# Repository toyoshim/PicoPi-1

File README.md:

# PicoPi-1
PDP-1 emulator, running on Raspberry Pi Pico, written in Rust.
See my [tweet](https://twitter.com/toyoshim/status/1591306173504188417?s=20&t=RCzo7QGhFZNQS9Ckd0akRA) to know how it looks like.

## Repository
This repository contains a KiCAD project, schematics and gerber data, for  the
DAC to covert X/Y CRT position in 10-bits ditial to analog signals so that
oscilloscopes can show picture in the XY mode.

Also, you can find a firmware under the `firmware` directory. It is written in
Rust, and you may need some setup to build it. This document doesn't explain
details (because I remember only partial setups...).

The project expects VS Code with some Extensions to develop ARM based processors
with openocd.

## TODO
- Speed control: now the emulation core counts cycles, but doesn't synchronized
with real timer. So, it runs a little faster than the original PDP-1.
- Game controller: yes, I know what I should do, but didn't implement it yet.
See my TODO comment in pdp1.rs's IOT instruction handling.
- Snowflake support: PDP-1 emulation core may have a bug around ALU as the
snowflake shows broken images. I have a working C++ version. So, it can be fixed
soon.
- Rust readability: as I'm new to Rust, the code still doesn't look so nice.
- Documents: agreed...

*CATS: ALL YOUR `PR` ARE WELCOMED TO US.*

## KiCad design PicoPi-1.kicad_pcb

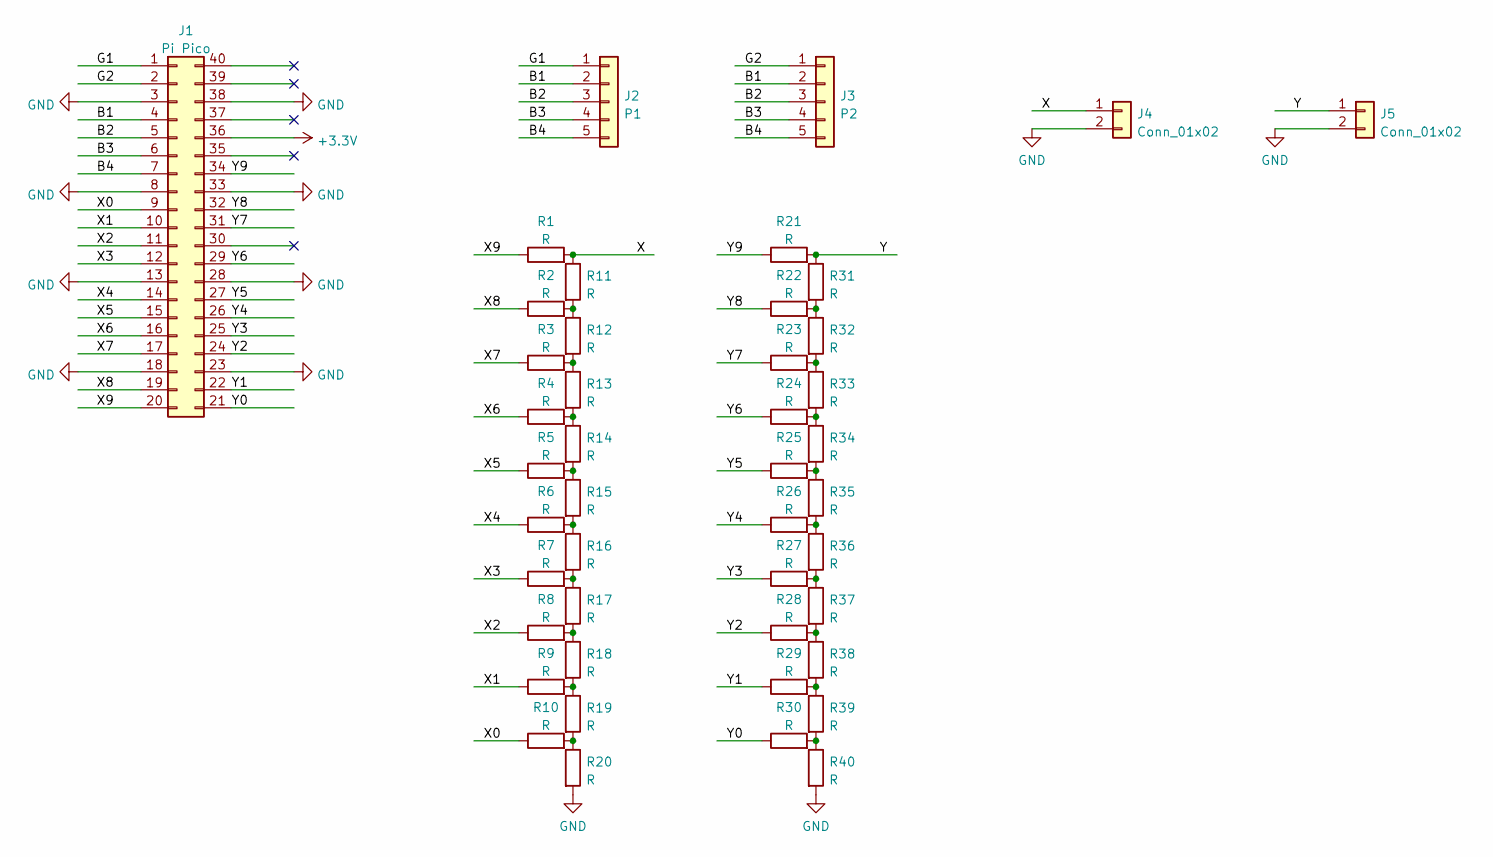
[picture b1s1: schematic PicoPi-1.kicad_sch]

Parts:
J1: Pi Pico; DIP-40_W17.78mm_PiPico
J2: P1; PinHeader_1x05_P2.54mm_Vertical
J3: P2; PinHeader_1x05_P2.54mm_Vertical
J4, J5: Conn_01x02; PinHeader_2x01_P2.54mm_Vertical
R1, R2, R3, R4, R5, R6, R7, R8, R9, R10, R11, R12, R13, R14, R15, R16, R17, R18, R19, R20, R21, R22, R23, R24, R25, R26, R27, R28, R29, R30, R31, R32, R33, R34, R35, R36, R37, R38, R39, R40: R; R_0603_1608Metric_Pad0.98x0.95mm_HandSolder

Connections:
+3.3V: J1.36
/B1: J1.4, J2.2, J3.2
/B2: J1.5, J2.3, J3.3
/B3: J1.6, J2.4, J3.4
/B4: J1.7, J2.5, J3.5
/G1: J1.1, J2.1
/G2: J1.2, J3.1
/X: J4.1, R1.2, R11.1
/X0: J1.9, R10.1
/X1: J1.10, R9.1
/X2: J1.11, R8.1
/X3: J1.12, R7.1
/X4: J1.14, R6.1
/X5: J1.15, R5.1
/X6: J1.16, R4.1
/X7: J1.17, R3.1
/X8: J1.19, R2.1
/X9: J1.20, R1.1
/Y: J5.1, R21.2, R31.1
/Y0: J1.21, R30.1
/Y1: J1.22, R29.1
/Y2: J1.24, R28.1
/Y3: J1.25, R27.1
/Y4: J1.26, R26.1
/Y5: J1.27, R25.1
/Y6: J1.29, R24.1
/Y7: J1.31, R23.1
/Y8: J1.32, R22.1
/Y9: J1.34, R21.1
GND: J1.3, J1.8, J1.13, J1.18, J1.23, J1.28, J1.33, J1.38, J4.2, J5.2, R20.2, R40.2
unnamed: R10.2, R19.2, R20.1
unnamed: R2.2, R11.2, R12.1
unnamed: R3.2, R12.2, R13.1
unnamed: R4.2, R13.2, R14.1
unnamed: R5.2, R14.2, R15.1
unnamed: R6.2, R15.2, R16.1
unnamed: R7.2, R16.2, R17.1
unnamed: R8.2, R17.2, R18.1
unnamed: R9.2, R18.2, R19.1
unnamed: R22.2, R31.2, R32.1
unnamed: R23.2, R32.2, R33.1
unnamed: R24.2, R33.2, R34.1
unnamed: R25.2, R34.2, R35.1
unnamed: R26.2, R35.2, R36.1
unnamed: R27.2, R36.2, R37.1
unnamed: R28.2, R37.2, R38.1
unnamed: R29.2, R38.2, R39.1
unnamed: R30.2, R39.2, R40.1

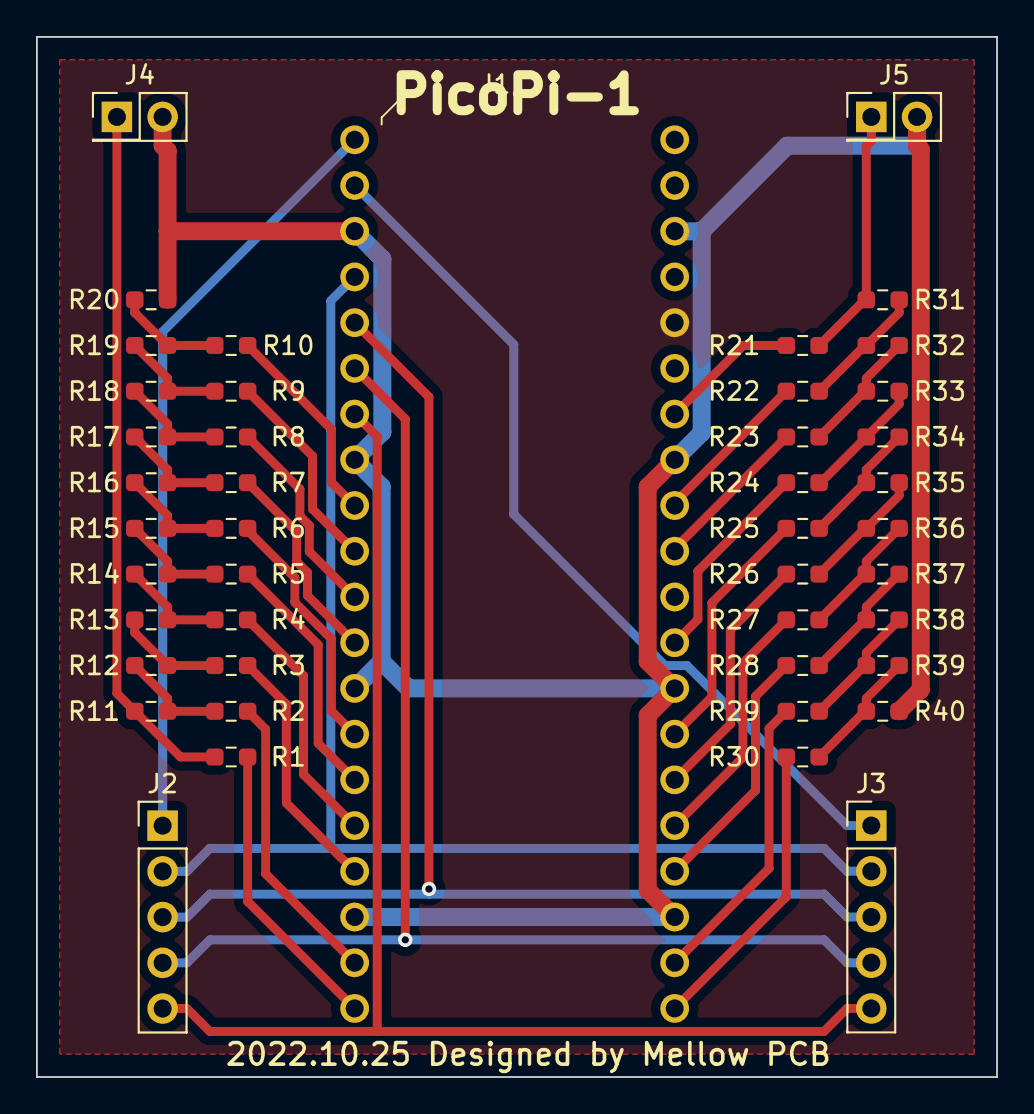
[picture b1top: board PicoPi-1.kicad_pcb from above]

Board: 2 copper layers, 53.3 x 57.8 mm, 45 parts (0 on the bottom side), 47 nets.

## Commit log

2022-10-28 update config and tools
2022-10-28 import generate files
2022-10-28 Add tools
2022-10-28 update settings
2022-10-28 implement rim bootstrap
2022-10-29 make the core modules as a lib and export them from lib.rs
    - also this change makes rim related code `no_std` compatible
2022-10-29 add core_memory and pdp1
2022-10-29 update: almost works
    - implement most pdp-1 ops except for SKP
    - fix rimconv to skip void period
    - update rim_spacewar (generated by the fixed rimconv)
2022-10-29 activate pico code path
2022-10-29 skp impl
    also fix a CLF bug that mask wasn't inverted
2022-11-11 Add copyright information
2022-11-11 implement pio
2022-11-12 Spacewar works with X/Y output
2022-11-12 typo
2022-11-12 Add a README.md
